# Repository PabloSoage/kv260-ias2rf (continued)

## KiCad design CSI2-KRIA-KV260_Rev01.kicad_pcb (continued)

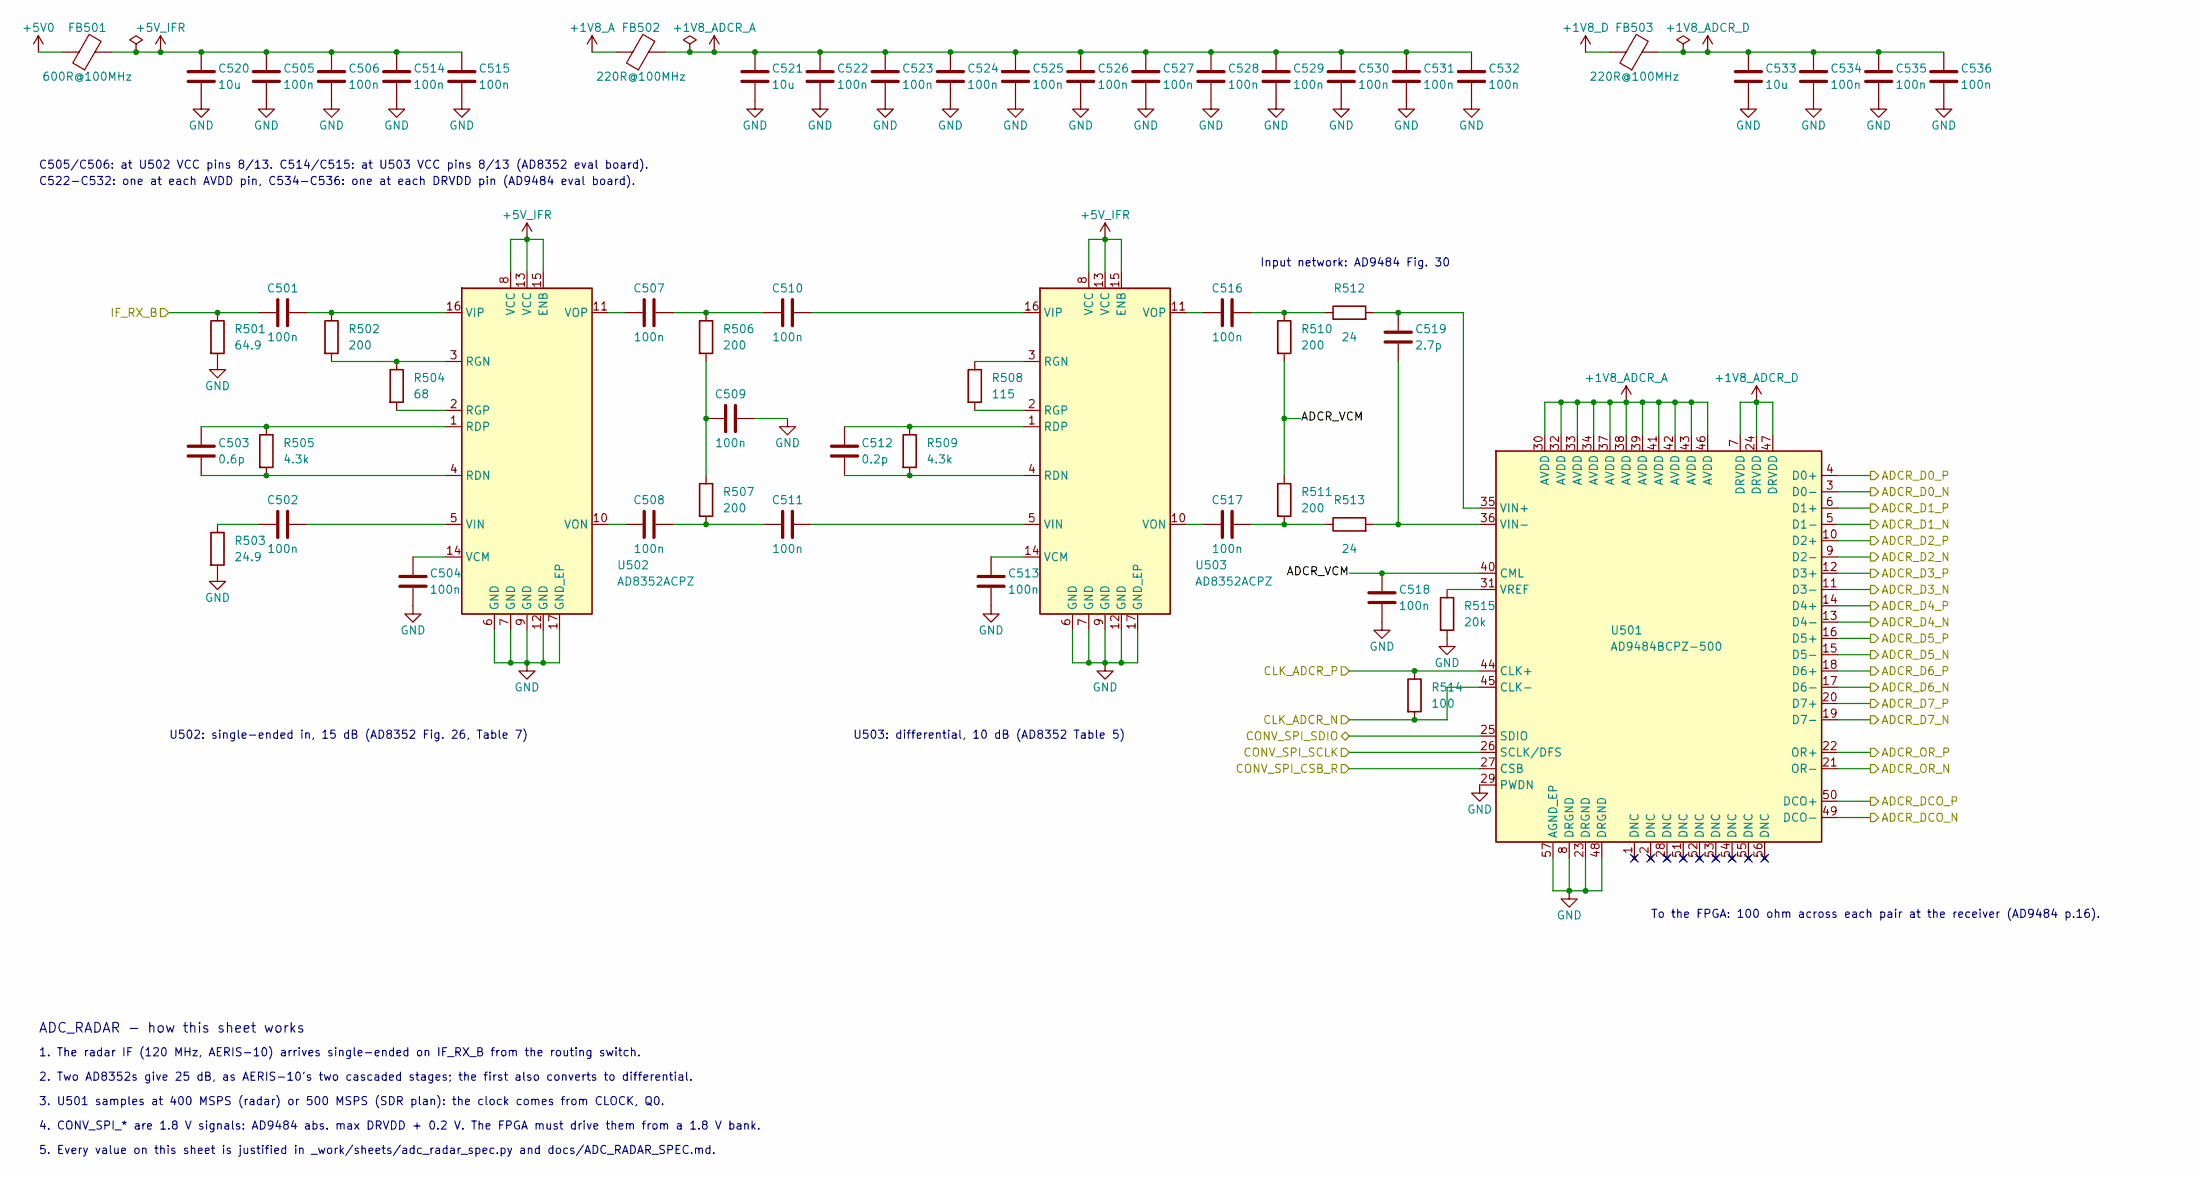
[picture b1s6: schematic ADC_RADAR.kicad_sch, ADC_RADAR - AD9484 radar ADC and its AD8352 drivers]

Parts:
C501, C502, C504, C505, C506, C507, C508, C509, C510, C511, C513, C514, C515, C516, C517, C518, C522, C523, C524, C525, C526, C527, C528, C529, C530, C531, C532, C534, C535, C536: 100n; C_0402_1005Metric
C503: 0.6p; C_0402_1005Metric
C512: 0.2p; C_0402_1005Metric
C519: 2.7p; C_0402_1005Metric
C520, C521, C533: 10u; C_0805_2012Metric
FB501: 600R@100MHz; L_0603_1608Metric
FB502, FB503: 220R@100MHz; L_0603_1608Metric
R501: 64.9; R_0402_1005Metric
R502, R506, R507, R510, R511: 200; R_0402_1005Metric
R503: 24.9; R_0402_1005Metric
R504: 68; R_0402_1005Metric
R505, R509: 4.3k; R_0402_1005Metric
R508: 115; R_0402_1005Metric
R512, R513: 24; R_0402_1005Metric
R514: 100; R_0402_1005Metric
R515: 20k; R_0402_1005Metric
U501: AD9484BCPZ-500; LFCSP-56-1EP_8x8mm_P0.5mm_EP5.1x5.1mm
U502, U503: AD8352ACPZ; LFCSP-16-1EP_3x3mm_P0.5mm_EP1.6x1.6mm

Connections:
+1V8_A: FB502.1; also elsewhere on the board
+1V8_ADCR_A: C521.1, C522.1, C523.1, C524.1, C525.1, C526.1, C527.1, C528.1, C529.1, C530.1, C531.1, C532.1, FB502.2, U501.30 (AVDD), U501.32 (AVDD), U501.33 (AVDD), U501.34 (AVDD), U501.37 (AVDD), U501.38 (AVDD), U501.39 (AVDD), U501.41 (AVDD), U501.42 (AVDD), U501.43 (AVDD), U501.46 (AVDD)
+1V8_ADCR_D: C533.1, C534.1, C535.1, C536.1, FB503.2, U501.7 (DRVDD), U501.24 (DRVDD), U501.47 (DRVDD)
+1V8_D: FB503.1; also elsewhere on the board
+5V0: FB501.1; also elsewhere on the board
+5V_IFR: C505.1, C506.1, C514.1, C515.1, C520.1, FB501.2, U502.8 (VCC), U502.13 (VCC), U502.15 (ENB), U503.8 (VCC), U503.13 (VCC), U503.15 (ENB)
/ADCR_D0_N: U501.3 (D0-); also elsewhere on the board
/ADCR_D0_P: U501.4 (D0+); also elsewhere on the board
/ADCR_D1_N: U501.5 (D1-); also elsewhere on the board
/ADCR_D1_P: U501.6 (D1+); also elsewhere on the board
/ADCR_D2_N: U501.9 (D2-); also elsewhere on the board
/ADCR_D2_P: U501.10 (D2+); also elsewhere on the board
/ADCR_D3_N: U501.11 (D3-); also elsewhere on the board
/ADCR_D3_P: U501.12 (D3+); also elsewhere on the board
/ADCR_D4_N: U501.13 (D4-); also elsewhere on the board
/ADCR_D4_P: U501.14 (D4+); also elsewhere on the board
/ADCR_D5_N: U501.15 (D5-); also elsewhere on the board
/ADCR_D5_P: U501.16 (D5+); also elsewhere on the board
/ADCR_D6_N: U501.17 (D6-); also elsewhere on the board
/ADCR_D6_P: U501.18 (D6+); also elsewhere on the board
/ADCR_D7_N: U501.19 (D7-); also elsewhere on the board
/ADCR_D7_P: U501.20 (D7+); also elsewhere on the board
/ADCR_DCO_N: U501.49 (DCO-); also elsewhere on the board
/ADCR_DCO_P: U501.50 (DCO+); also elsewhere on the board
/ADCR_OR_N: U501.21 (OR-); also elsewhere on the board
/ADCR_OR_P: U501.22 (OR+); also elsewhere on the board
/ADC_RADAR/ADCR_VCM: C518.1, R510.2, R511.1, U501.40 (CML)
/CLK_ADCR_N: R514.2, U501.45 (CLK-); also elsewhere on the board
/CLK_ADCR_P: R514.1, U501.44 (CLK+); also elsewhere on the board
/CONV_SPI_CSB_R: U501.27 (CSB); also elsewhere on the board
/CONV_SPI_SCLK: U501.26 (SCLK/DFS); also elsewhere on the board
/CONV_SPI_SDIO: U501.25 (SDIO); also elsewhere on the board
/IF_RX_B: C501.1, R501.1; also elsewhere on the board
GND: C504.2, C505.2, C506.2, C509.2, C513.2, C514.2, C515.2, C518.2, C520.2, C521.2, C522.2, C523.2, C524.2, C525.2, C526.2, C527.2, C528.2, C529.2, C530.2, C531.2, C532.2, C533.2, C534.2, C535.2, C536.2, R501.2, R503.2, R515.2, U501.8 (DRGND), U501.23 (DRGND), U501.29 (PWDN), U501.48 (DRGND), U501.57 (AGND_EP), U502.6 (GND), U502.7 (GND), U502.9 (GND), U502.12 (GND), U502.17 (GND_EP), U503.6 (GND), U503.7 (GND), U503.9 (GND), U503.12 (GND), U503.17 (GND_EP); also elsewhere on the board
unnamed: C502.1, R503.1
unnamed: C507.2, C510.1, R506.1
unnamed: C508.2, C511.1, R507.2
unnamed: C509.1, R506.2, R507.1
unnamed: C516.2, R510.1, R512.1
unnamed: C517.2, R511.2, R513.1
unnamed: C519.1, R512.2, U501.35 (VIN+)
unnamed: C519.2, R513.2, U501.36 (VIN-)
unnamed: R515.1, U501.31 (VREF)
unnamed: C503.2, R505.2, U502.4 (RDN)
unnamed: C503.1, R505.1, U502.1 (RDP)
unnamed: R502.2, R504.1, U502.3 (RGN)
unnamed: R504.2, U502.2 (RGP)
unnamed: C504.1, U502.14 (VCM)
unnamed: C502.2, U502.5 (VIN)
unnamed: C501.2, R502.1, U502.16 (VIP)
unnamed: C508.1, U502.10 (VON)
unnamed: C507.1, U502.11 (VOP)
unnamed: C512.2, R509.2, U503.4 (RDN)
unnamed: C512.1, R509.1, U503.1 (RDP)
unnamed: R508.1, U503.3 (RGN)
unnamed: R508.2, U503.2 (RGP)
unnamed: C513.1, U503.14 (VCM)
unnamed: C511.2, U503.5 (VIN)
unnamed: C510.2, U503.16 (VIP)
unnamed: C517.1, U503.10 (VON)
unnamed: C516.1, U503.11 (VOP)

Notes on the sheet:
C505/C506: at U502 VCC pins 8/13. C514/C515: at U503 VCC pins 8/13 (AD8352 eval board).
C522-C532: one at each AVDD pin, C534-C536: one at each DRVDD pin (AD9484 eval board).
U502: single-ended in, 15 dB (AD8352 Fig. 26, Table 7)
U503: differential, 10 dB (AD8352 Table 5)
Input network: AD9484 Fig. 30
To the FPGA: 100 ohm across each pair at the receiver (AD9484 p.16).
ADC_RADAR - how this sheet works
1. The radar IF (120 MHz, AERIS-10) arrives single-ended on IF_RX_B from the routing switch.
2. Two AD8352s give 25 dB, as AERIS-10's two cascaded stages; the first also converts to differential.
3. U501 samples at 400 MSPS (radar) or 500 MSPS (SDR plan): the clock comes from CLOCK, Q0.
4. CONV_SPI_* are 1.8 V signals: AD9484 abs. max DRVDD + 0.2 V. The FPGA must drive them from a 1.8 V bank.
5. Every value on this sheet is justified in _work/sheets/adc_radar_spec.py and docs/ADC_RADAR_SPEC.md.

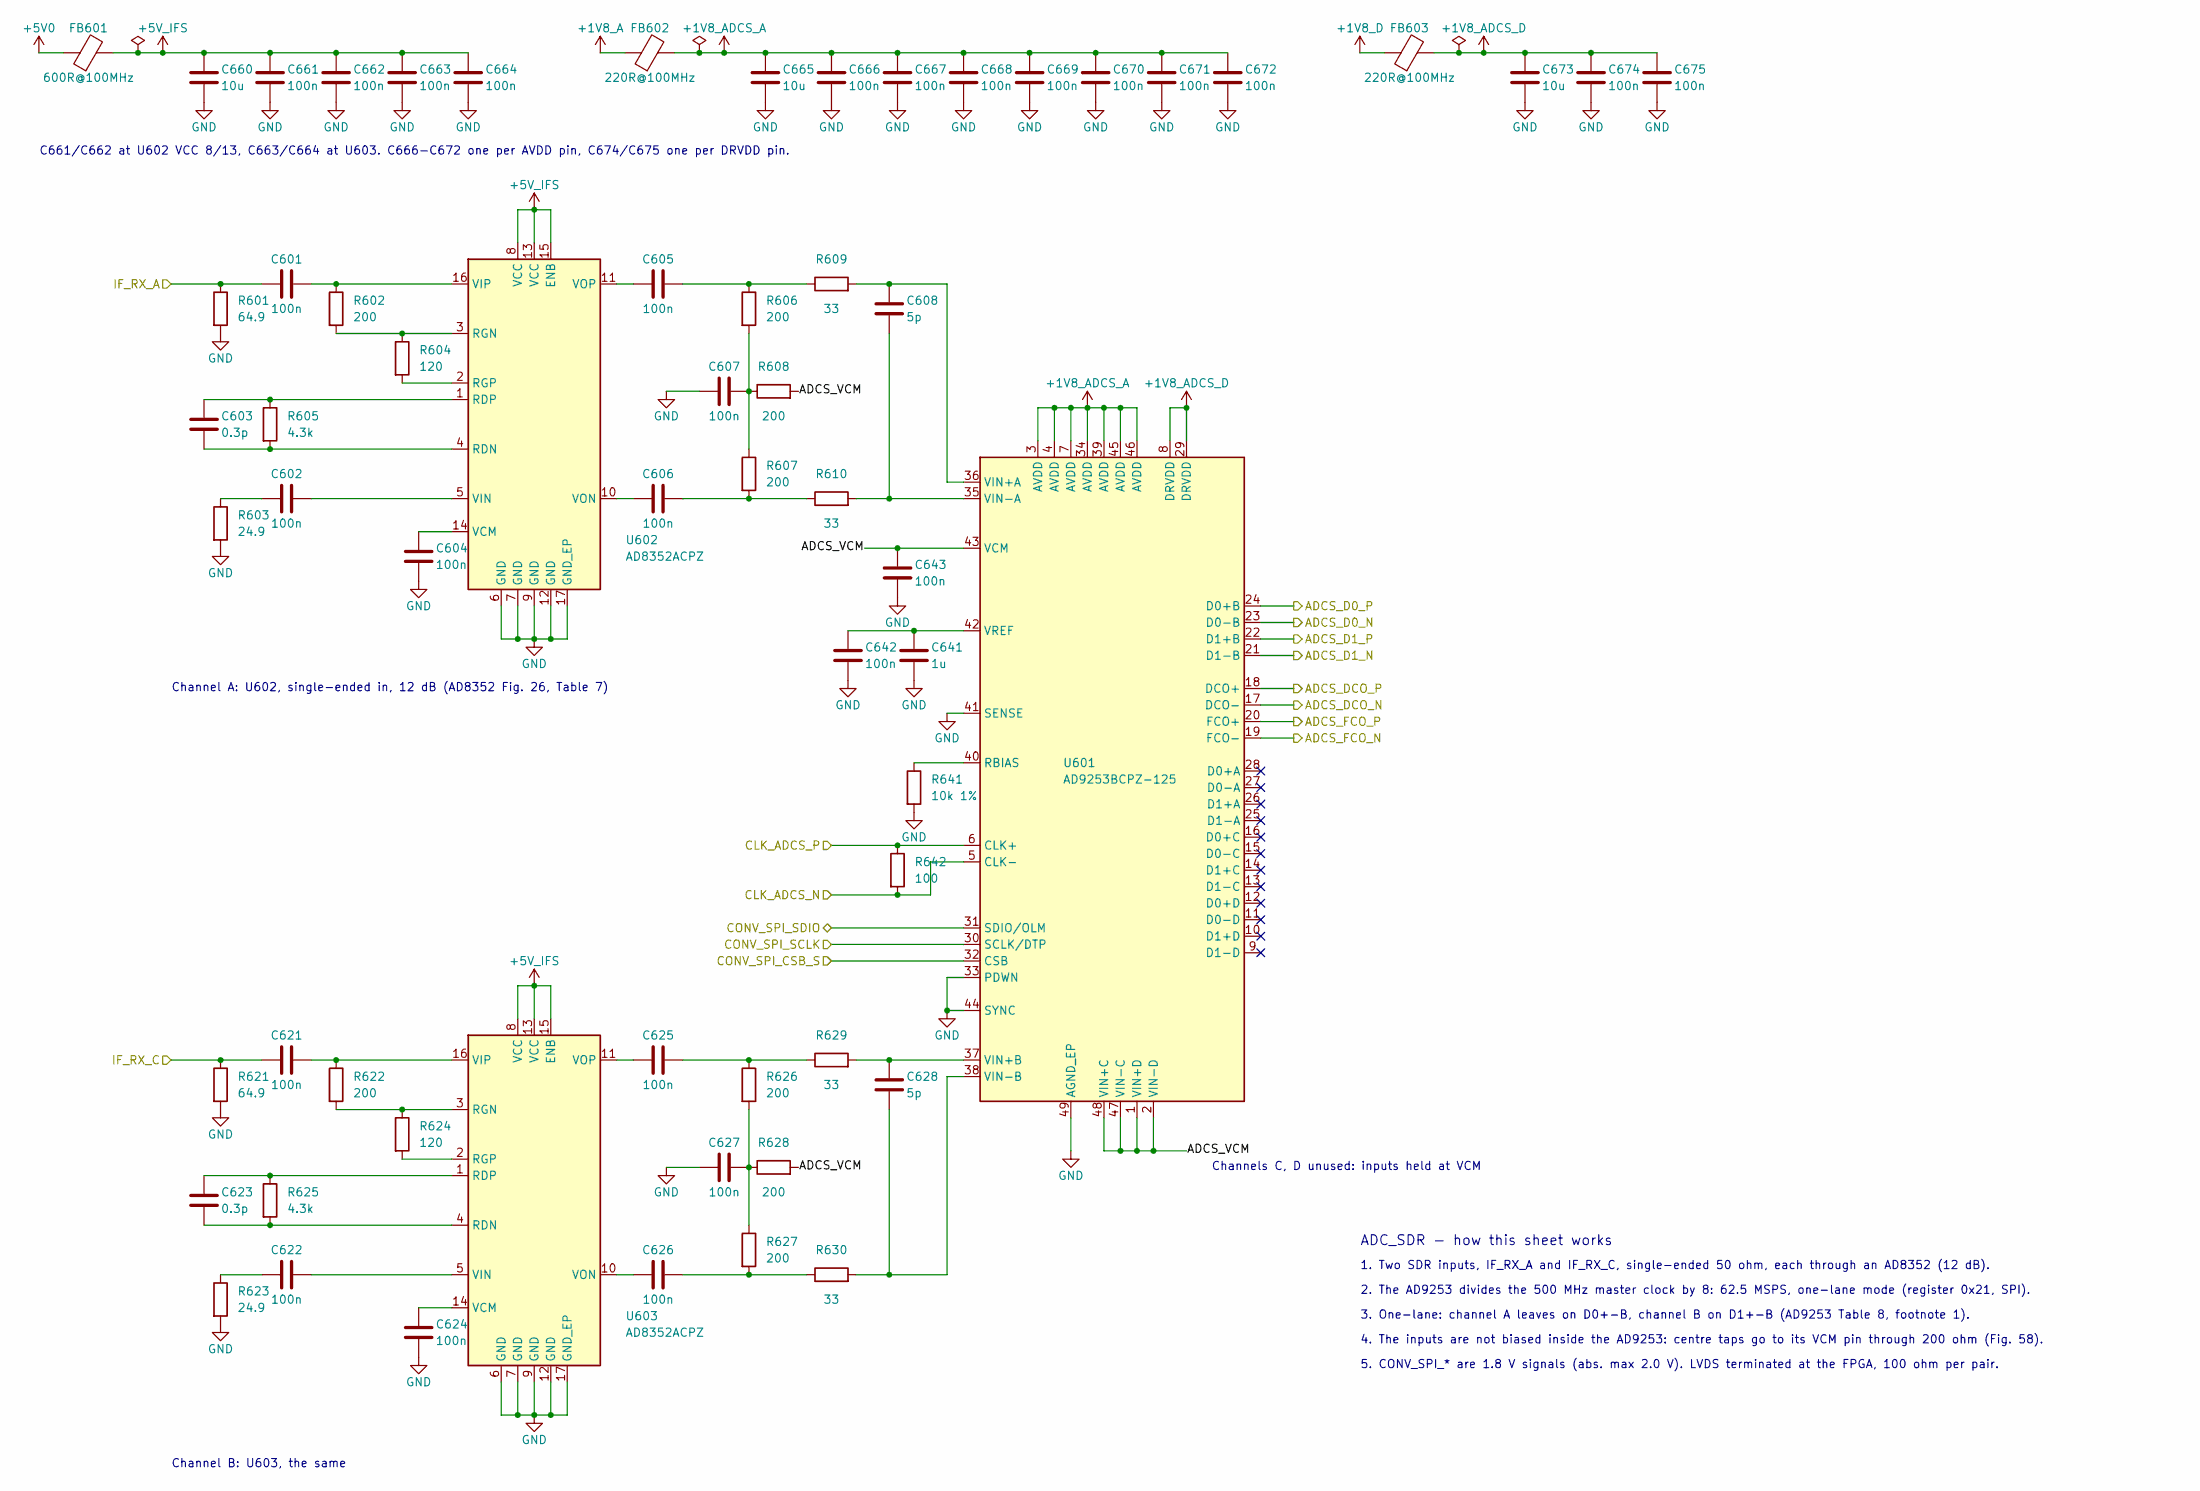
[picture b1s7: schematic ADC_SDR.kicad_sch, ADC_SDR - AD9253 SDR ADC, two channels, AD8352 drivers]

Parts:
C601, C602, C604, C605, C606, C607, C621, C622, C624, C625, C626, C627, C642, C643, C661, C662, C663, C664, C666, C667, C668, C669, C670, C671, C672, C674, C675: 100n; C_0402_1005Metric
C603, C623: 0.3p; C_0402_1005Metric
C608, C628: 5p; C_0402_1005Metric
C641: 1u; C_0402_1005Metric
C660, C665, C673: 10u; C_0805_2012Metric
FB601: 600R@100MHz; L_0603_1608Metric
FB602, FB603: 220R@100MHz; L_0603_1608Metric
R601, R621: 64.9; R_0402_1005Metric
R602, R606, R607, R608, R622, R626, R627, R628: 200; R_0402_1005Metric
R603, R623: 24.9; R_0402_1005Metric
R604, R624: 120; R_0402_1005Metric
R605, R625: 4.3k; R_0402_1005Metric
R609, R610, R629, R630: 33; R_0402_1005Metric
R641: 10k 1%; R_0402_1005Metric
R642: 100; R_0402_1005Metric
U601: AD9253BCPZ-125; QFN-48-1EP_7x7mm_P0.5mm_EP5.6x5.6mm
U602, U603: AD8352ACPZ; LFCSP-16-1EP_3x3mm_P0.5mm_EP1.6x1.6mm

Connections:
+1V8_A: FB602.1; also elsewhere on the board
+1V8_ADCS_A: C665.1, C666.1, C667.1, C668.1, C669.1, C670.1, C671.1, C672.1, FB602.2, U601.3 (AVDD), U601.4 (AVDD), U601.7 (AVDD), U601.34 (AVDD), U601.39 (AVDD), U601.45 (AVDD), U601.46 (AVDD)
+1V8_ADCS_D: C673.1, C674.1, C675.1, FB603.2, U601.8 (DRVDD), U601.29 (DRVDD)
+1V8_D: FB603.1; also elsewhere on the board
+5V0: FB601.1; also elsewhere on the board
+5V_IFS: C660.1, C661.1, C662.1, C663.1, C664.1, FB601.2, U602.8 (VCC), U602.13 (VCC), U602.15 (ENB), U603.8 (VCC), U603.13 (VCC), U603.15 (ENB)
/ADCS_D0_N: U601.23 (D0-B); also elsewhere on the board
/ADCS_D0_P: U601.24 (D0+B); also elsewhere on the board
/ADCS_D1_N: U601.21 (D1-B); also elsewhere on the board
/ADCS_D1_P: U601.22 (D1+B); also elsewhere on the board
/ADCS_DCO_N: U601.17 (DCO-); also elsewhere on the board
/ADCS_DCO_P: U601.18 (DCO+); also elsewhere on the board
/ADCS_FCO_N: U601.19 (FCO-); also elsewhere on the board
/ADCS_FCO_P: U601.20 (FCO+); also elsewhere on the board
/ADC_SDR/ADCS_VCM: C643.1, R608.2, R628.2, U601.1 (VIN+D), U601.2 (VIN-D), U601.43 (VCM), U601.47 (VIN-C), U601.48 (VIN+C)
/CLK_ADCS_N: R642.2, U601.5 (CLK-); also elsewhere on the board
/CLK_ADCS_P: R642.1, U601.6 (CLK+); also elsewhere on the board
/CONV_SPI_CSB_S: U601.32 (CSB); also elsewhere on the board
/CONV_SPI_SCLK: U601.30 (SCLK/DTP); also elsewhere on the board
/CONV_SPI_SDIO: U601.31 (SDIO/OLM); also elsewhere on the board
/IF_RX_A: C601.1, R601.1; also elsewhere on the board
/IF_RX_C: C621.1, R621.1; also elsewhere on the board
GND: C604.2, C607.1, C624.2, C627.1, C641.2, C642.2, C643.2, C660.2, C661.2, C662.2, C663.2, C664.2, C665.2, C666.2, C667.2, C668.2, C669.2, C670.2, C671.2, C672.2, C673.2, C674.2, C675.2, R601.2, R603.2, R621.2, R623.2, R641.2, U601.33 (PDWN), U601.41 (SENSE), U601.44 (SYNC), U601.49 (AGND_EP), U602.6 (GND), U602.7 (GND), U602.9 (GND), U602.12 (GND), U602.17 (GND_EP), U603.6 (GND), U603.7 (GND), U603.9 (GND), U603.12 (GND), U603.17 (GND_EP); also elsewhere on the board
unnamed: C602.1, R603.1
unnamed: C605.2, R606.1, R609.1
unnamed: C606.2, R607.2, R610.1
unnamed: C607.2, R606.2, R607.1, R608.1
unnamed: C622.1, R623.1
unnamed: C625.2, R626.1, R629.1
unnamed: C626.2, R627.2, R630.1
unnamed: C627.2, R626.2, R627.1, R628.1
unnamed: R641.1, U601.40 (RBIAS)
unnamed: C608.1, R609.2, U601.36 (VIN+A)
unnamed: C628.1, R629.2, U601.37 (VIN+B)
unnamed: C608.2, R610.2, U601.35 (VIN-A)
unnamed: C628.2, R630.2, U601.38 (VIN-B)
unnamed: C641.1, C642.1, U601.42 (VREF)
unnamed: C603.2, R605.2, U602.4 (RDN)
unnamed: C603.1, R605.1, U602.1 (RDP)
unnamed: R602.2, R604.1, U602.3 (RGN)
unnamed: R604.2, U602.2 (RGP)
unnamed: C604.1, U602.14 (VCM)
unnamed: C602.2, U602.5 (VIN)
unnamed: C601.2, R602.1, U602.16 (VIP)
unnamed: C606.1, U602.10 (VON)
unnamed: C605.1, U602.11 (VOP)
unnamed: C623.2, R625.2, U603.4 (RDN)
unnamed: C623.1, R625.1, U603.1 (RDP)
unnamed: R622.2, R624.1, U603.3 (RGN)
unnamed: R624.2, U603.2 (RGP)
unnamed: C624.1, U603.14 (VCM)
unnamed: C622.2, U603.5 (VIN)
unnamed: C621.2, R622.1, U603.16 (VIP)
unnamed: C626.1, U603.10 (VON)
unnamed: C625.1, U603.11 (VOP)

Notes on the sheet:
C661/C662 at U602 VCC 8/13, C663/C664 at U603. C666-C672 one per AVDD pin, C674/C675 one per DRVDD pin.
Channel A: U602, single-ended in, 12 dB (AD8352 Fig. 26, Table 7)
Channel B: U603, the same
Channels C, D unused: inputs held at VCM
ADC_SDR - how this sheet works
1. Two SDR inputs, IF_RX_A and IF_RX_C, single-ended 50 ohm, each through an AD8352 (12 dB).
2. The AD9253 divides the 500 MHz master clock by 8: 62.5 MSPS, one-lane mode (register 0x21, SPI).
3. One-lane: channel A leaves on D0+-B, channel B on D1+-B (AD9253 Table 8, footnote 1).
4. The inputs are not biased inside the AD9253: centre taps go to its VCM pin through 200 ohm (Fig. 58).
5. CONV_SPI_* are 1.8 V signals (abs. max 2.0 V). LVDS terminated at the FPGA, 100 ohm per pair.

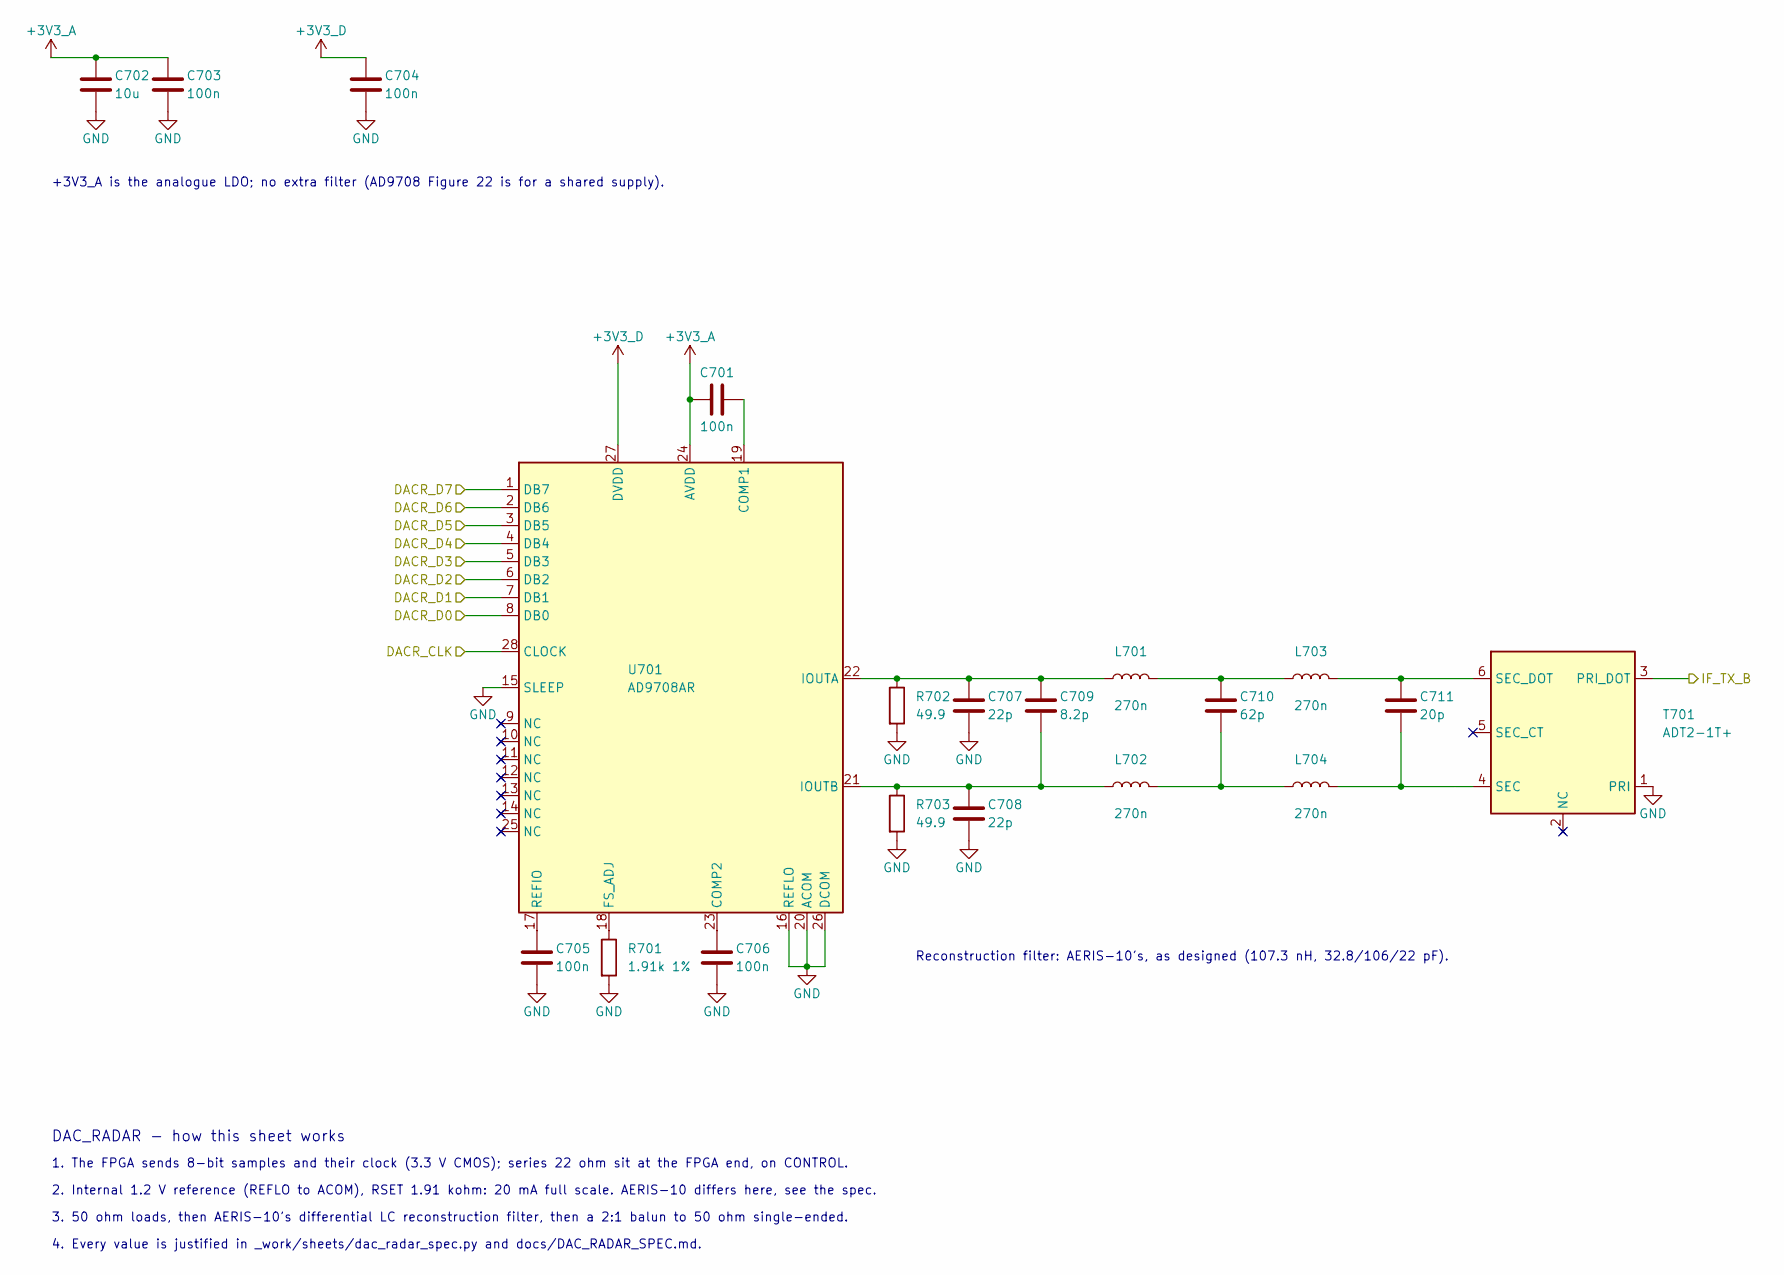
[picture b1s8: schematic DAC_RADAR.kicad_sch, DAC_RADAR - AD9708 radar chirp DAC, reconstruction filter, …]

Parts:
C701, C703, C704, C705, C706: 100n; C_0402_1005Metric
C702: 10u; C_0805_2012Metric
C707, C708: 22p; C_0402_1005Metric
C709: 8.2p; C_0402_1005Metric
C710: 62p; C_0402_1005Metric
C711: 20p; C_0402_1005Metric
L701, L702, L703, L704: 270n; L_0603_1608Metric
R701: 1.91k 1%; R_0402_1005Metric
R702, R703: 49.9; R_0402_1005Metric
T701: ADT2-1T+; Mini-Circuits_CD542_H2.84mm
U701: AD9708AR; SOIC-28W_7.5x17.9mm_P1.27mm

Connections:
+3V3_A: C701.1, C702.1, C703.1, U701.24 (AVDD); also elsewhere on the board
+3V3_D: C704.1, U701.27 (DVDD); also elsewhere on the board
/DACR_CLK: U701.28 (CLOCK); also elsewhere on the board
/DACR_D0: U701.8 (DB0); also elsewhere on the board
/DACR_D1: U701.7 (DB1); also elsewhere on the board
/DACR_D2: U701.6 (DB2); also elsewhere on the board
/DACR_D3: U701.5 (DB3); also elsewhere on the board
/DACR_D4: U701.4 (DB4); also elsewhere on the board
/DACR_D5: U701.3 (DB5); also elsewhere on the board
/DACR_D6: U701.2 (DB6); also elsewhere on the board
/DACR_D7: U701.1 (DB7); also elsewhere on the board
/IF_TX_B: T701.3 (PRI_DOT); also elsewhere on the board
GND: C702.2, C703.2, C704.2, C705.2, C706.2, C707.2, C708.2, R701.2, R702.2, R703.2, T701.1 (PRI), U701.15 (SLEEP), U701.16 (REFLO), U701.20 (ACOM), U701.26 (DCOM); also elsewhere on the board
unnamed: C710.1, L701.2, L703.1
unnamed: C710.2, L702.2, L704.1
unnamed: C711.2, L704.2, T701.4 (SEC)
unnamed: C711.1, L703.2, T701.6 (SEC_DOT)
unnamed: C701.2, U701.19 (COMP1)
unnamed: C706.1, U701.23 (COMP2)
unnamed: R701.1, U701.18 (FS_ADJ)
unnamed: C707.1, C709.1, L701.1, R702.1, U701.22 (IOUTA)
unnamed: C708.1, C709.2, L702.1, R703.1, U701.21 (IOUTB)
unnamed: C705.1, U701.17 (REFIO)

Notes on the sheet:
+3V3_A is the analogue LDO; no extra filter (AD9708 Figure 22 is for a shared supply).
Reconstruction filter: AERIS-10's, as designed (107.3 nH, 32.8/106/22 pF).
DAC_RADAR - how this sheet works
1. The FPGA sends 8-bit samples and their clock (3.3 V CMOS); series 22 ohm sit at the FPGA end, on CONTROL.
2. Internal 1.2 V reference (REFLO to ACOM), RSET 1.91 kohm: 20 mA full scale. AERIS-10 differs here, see the spec.
3. 50 ohm loads, then AERIS-10's differential LC reconstruction filter, then a 2:1 balun to 50 ohm single-ended.
4. Every value is justified in _work/sheets/dac_radar_spec.py and docs/DAC_RADAR_SPEC.md.

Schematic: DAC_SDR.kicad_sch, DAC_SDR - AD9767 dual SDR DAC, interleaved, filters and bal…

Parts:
C801, C805, C806, C807: 100n; C_0402_1005Metric
C802, C803: 22n; C_0402_1005Metric
C804, C808: 10u; C_0805_2012Metric
C811, C812, C831, C832: 22p; C_0402_1005Metric
C813, C833: 8.2p; C_0402_1005Metric
C814, C834: 62p; C_0402_1005Metric
C815, C835: 20p; C_0402_1005Metric
L811, L812, L813, L814, L831, L832, L833, L834: 270n; L_0603_1608Metric
R801, R803: 3.83k; R_0402_1005Metric
R802, R804: 255; R_0402_1005Metric
R811, R812, R831, R832: 49.9; R_0402_1005Metric
T801, T802: ADT2-1T+; Mini-Circuits_CD542_H2.84mm
U801: AD9767ASTZ; LQFP-48_7x7mm_P0.5mm

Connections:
+3V3_A: C804.1, C805.1, U801.47 (AVDD); also elsewhere on the board
+3V3_D: C806.1, C807.1, C808.1, U801.16 (DVDD1), U801.22 (DVDD2); also elsewhere on the board
/DACS_D0: U801.14 (DB0P1); also elsewhere on the board
/DACS_D1: U801.13 (DB1P1); also elsewhere on the board
/DACS_D2: U801.12 (DB2P1); also elsewhere on the board
/DACS_D3: U801.11 (DB3P1); also elsewhere on the board
/DACS_D4: U801.10 (DB4P1); also elsewhere on the board
/DACS_D5: U801.9 (DB5P1); also elsewhere on the board
/DACS_D6: U801.8 (DB6P1); also elsewhere on the board
/DACS_D7: U801.7 (DB7P1); also elsewhere on the board
/DACS_D8: U801.6 (DB8P1); also elsewhere on the board
/DACS_D9: U801.5 (DB9P1); also elsewhere on the board
/DACS_D10: U801.4 (DB10P1); also elsewhere on the board
/DACS_D11: U801.3 (DB11P1); also elsewhere on the board
/DACS_D12: U801.2 (DB12P1); also elsewhere on the board
/DACS_D13: U801.1 (DB13P1); also elsewhere on the board
/DACS_IQCLK: U801.18 (CLK1/IQCLK); also elsewhere on the board
/DACS_IQRESET: U801.19 (CLK2/IQRESET); also elsewhere on the board
/DACS_IQSEL: U801.20 (WRT2/IQSEL); also elsewhere on the board
/DACS_IQWRT: U801.17 (WRT1/IQWRT); also elsewhere on the board
/IF_TX_A: T801.3 (PRI_DOT); also elsewhere on the board
/IF_TX_C: T802.3 (PRI_DOT); also elsewhere on the board
GND: C801.2, C802.2, C803.2, C804.2, C805.2, C806.2, C807.2, C808.2, C811.2, C812.2, C831.2, C832.2, R801.2, R803.2, R811.2, R812.2, R831.2, R832.2, T801.1 (PRI), T802.1 (PRI), U801.15 (DCOM1), U801.21 (DCOM2), U801.23 (DB13P2), U801.24 (DB12P2), U801.25 (DB11P2), U801.26 (DB10P2), U801.27 (DB9P2), U801.28 (DB8P2), U801.29 (DB7P2), U801.30 (DB6P2), U801.31 (DB5P2), U801.32 (DB4P2), U801.33 (DB3P2), U801.34 (DB2P2), U801.35 (DB1P2), U801.36 (DB0P2), U801.37 (SLEEP), U801.38 (ACOM), U801.42 (GAINCTRL), U801.48 (MODE); also elsewhere on the board
unnamed: C802.1, R802.2
unnamed: C803.1, R804.2
unnamed: C814.1, L811.2, L813.1
unnamed: C814.2, L812.2, L814.1
unnamed: C834.1, L831.2, L833.1
unnamed: C834.2, L832.2, L834.1
unnamed: C815.2, L814.2, T801.4 (SEC)
unnamed: C815.1, L813.2, T801.6 (SEC_DOT)
unnamed: C835.2, L834.2, T802.4 (SEC)
unnamed: C835.1, L833.2, T802.6 (SEC_DOT)
unnamed: R801.1, R802.1, U801.44 (FSADJ1)
unnamed: R803.1, R804.1, U801.41 (FSADJ2)
unnamed: C811.1, C813.1, L811.1, R811.1, U801.46 (IOUTA1)
unnamed: C831.1, C833.1, L831.1, R831.1, U801.39 (IOUTA2)
unnamed: C812.1, C813.2, L812.1, R812.1, U801.45 (IOUTB1)
unnamed: C832.1, C833.2, L832.1, R832.1, U801.40 (IOUTB2)
unnamed: C801.1, U801.43 (REFIO)

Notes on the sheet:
C805 at AVDD pin 47; C806, C807 at DVDD1/DVDD2 pins 16/22.
DAC1 -> IF_TX_A, DAC2 -> IF_TX_C. Filters: AERIS-10's, as on DAC_RADAR.
DAC_SDR - how this sheet works
1. Interleaved mode (MODE low): the FPGA writes I and Q alternately on one 14-bit port; IQSEL steers each word.
2. IQCLK is divided by 2 inside; IQRESET aligns the pair. Series 22 ohm on the data sit at the FPGA, on CONTROL.
3. Internal 1.2 V reference; RSET 3.83 kohm per DAC = 10 mA, 0.5 V on 49.9 ohm: best distortion (p.24).
4. Every value is justified in _work/sheets/dac_sdr_spec.py and docs/DAC_SDR_SPEC.md.

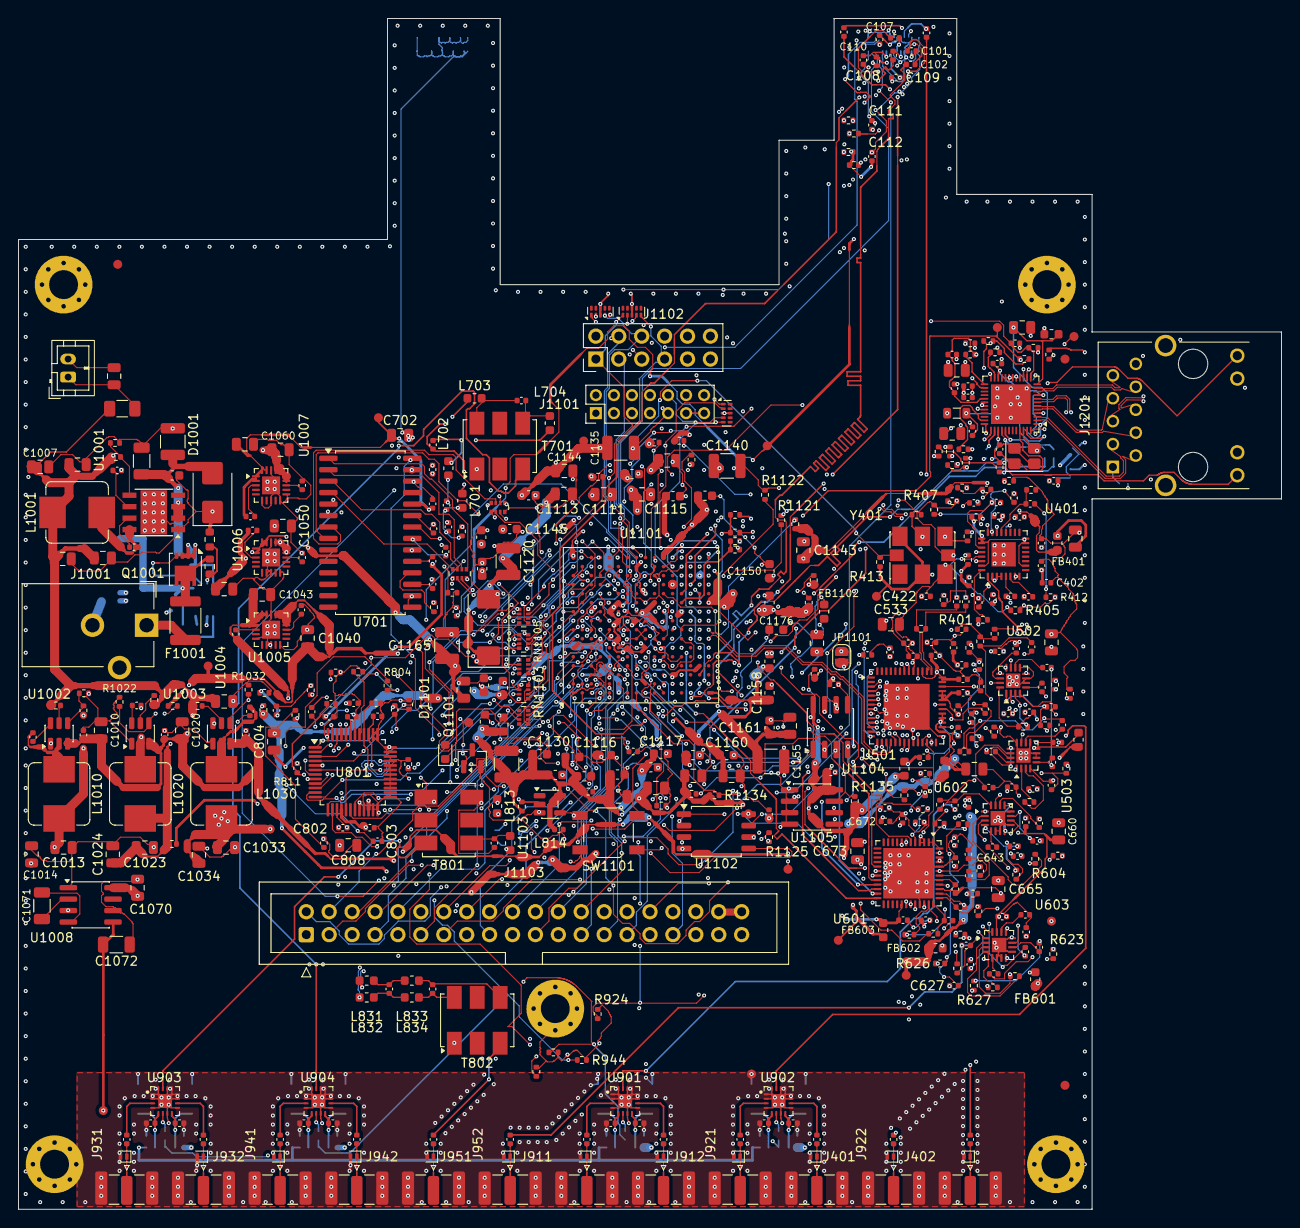
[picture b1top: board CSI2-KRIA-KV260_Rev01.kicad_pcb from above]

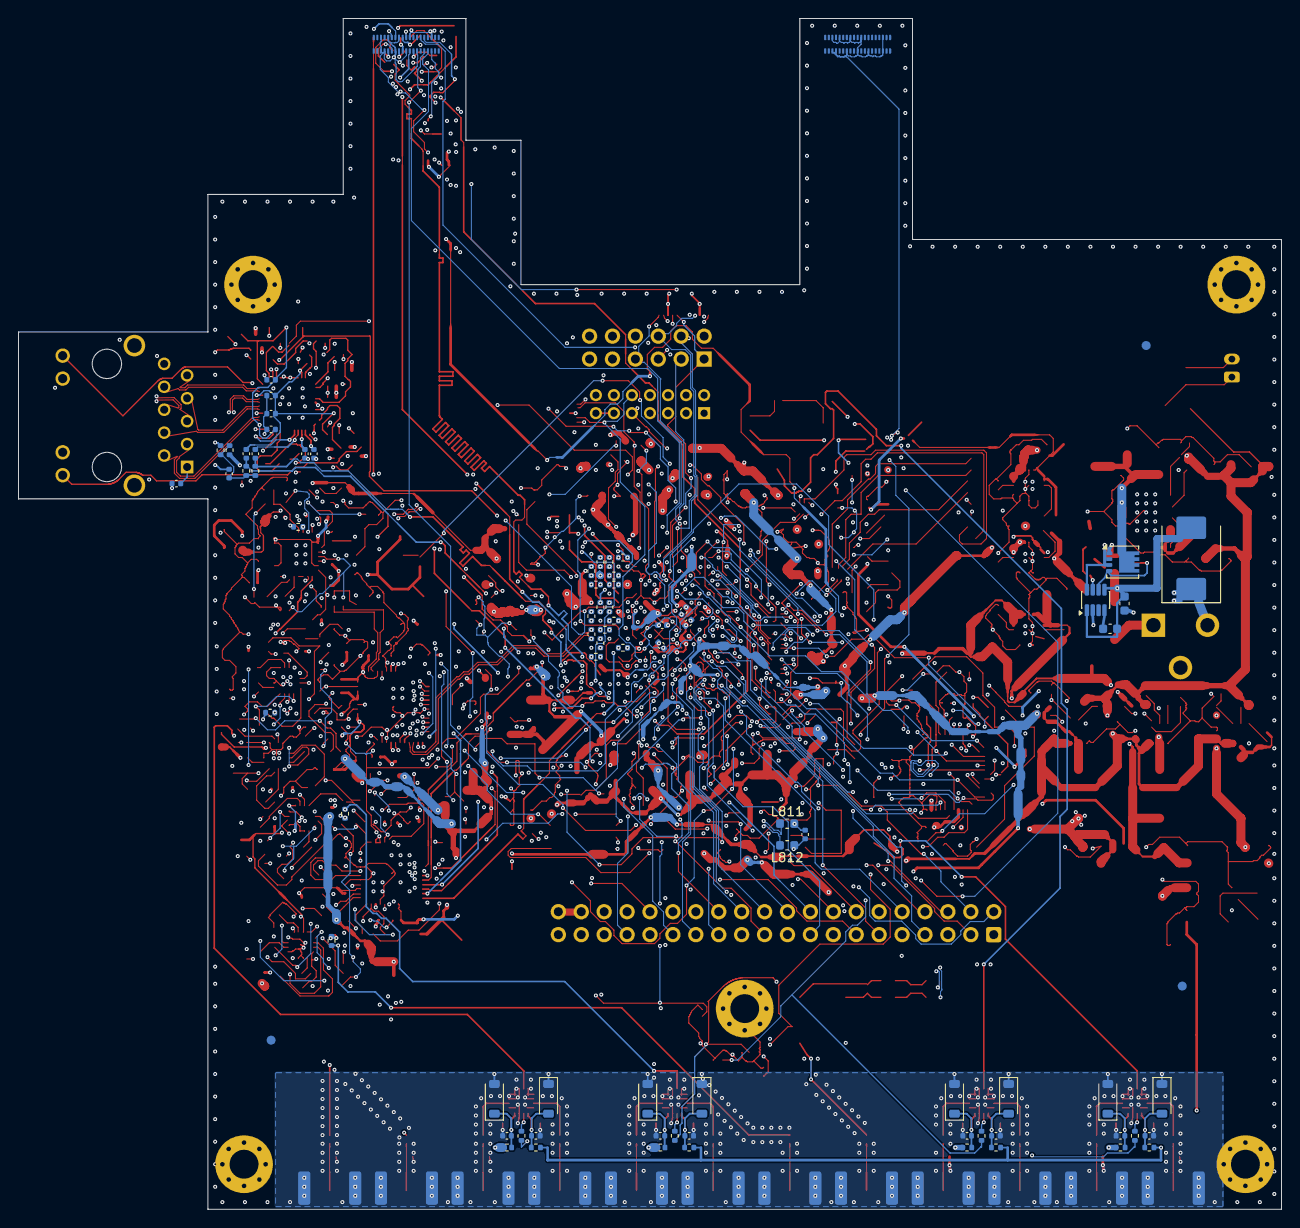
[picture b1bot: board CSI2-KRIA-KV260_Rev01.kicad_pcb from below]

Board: 8 copper layers, 140.0 x 132.0 mm, 578 parts (79 on the bottom side), 420 nets.

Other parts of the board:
FID1, FID2, FID3, FID4, FID5, FID6: Fiducial_1mm_Mask2mm
H1, H2, H3, H4, H5: MountingHole_3.2mm_M3_Pad_Via
TP1: +5V0; TestPad_D1.0mm_BoardOnly
TP2: +3V3_D; TestPad_D1.0mm_BoardOnly
TP3: +3V3_A; TestPad_D1.0mm_BoardOnly
TP4: +2V5; TestPad_D1.0mm_BoardOnly
TP5: +1V8_D; TestPad_D1.0mm_BoardOnly
TP6: +1V8_A; TestPad_D1.0mm_BoardOnly
TP7: +1V2; TestPad_D1.0mm_BoardOnly
TP8: +1V0; TestPad_D1.0mm_BoardOnly
TP9: -3V3; TestPad_D1.0mm_BoardOnly
TP10: +3V3_CLK; TestPad_D1.0mm_BoardOnly
TP11: DONE; TestPad_D1.0mm_BoardOnly
TP12, TP13: GND; TestPad_D1.0mm_BoardOnly
TP14: MDC; TestPad_D1.0mm_BoardOnly
TP15: MDIO; TestPad_D1.0mm_BoardOnly

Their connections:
+1V0: TP8.1; also elsewhere on the board
+1V2: TP7.1; also elsewhere on the board
+1V8_A: TP6.1; also elsewhere on the board
+1V8_D: TP5.1; also elsewhere on the board
+2V5: TP4.1; also elsewhere on the board
+3V3_A: TP3.1; also elsewhere on the board
+3V3_CLK: TP10.1; also elsewhere on the board
+3V3_D: TP2.1; also elsewhere on the board
+5V0: TP1.1; also elsewhere on the board
-3V3: TP9.1; also elsewhere on the board
/CONTROL/DONE: TP11.1; also elsewhere on the board
/CONTROL/ETH_MDC: TP14.1; also elsewhere on the board
/CONTROL/ETH_MDIO: TP15.1; also elsewhere on the board
GND: H1.1, H2.1, H3.1, H4.1, H5.1, TP12.1, TP13.1; also elsewhere on the board
